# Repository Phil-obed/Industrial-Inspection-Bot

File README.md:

download TINYGPS++ library for successful compilation

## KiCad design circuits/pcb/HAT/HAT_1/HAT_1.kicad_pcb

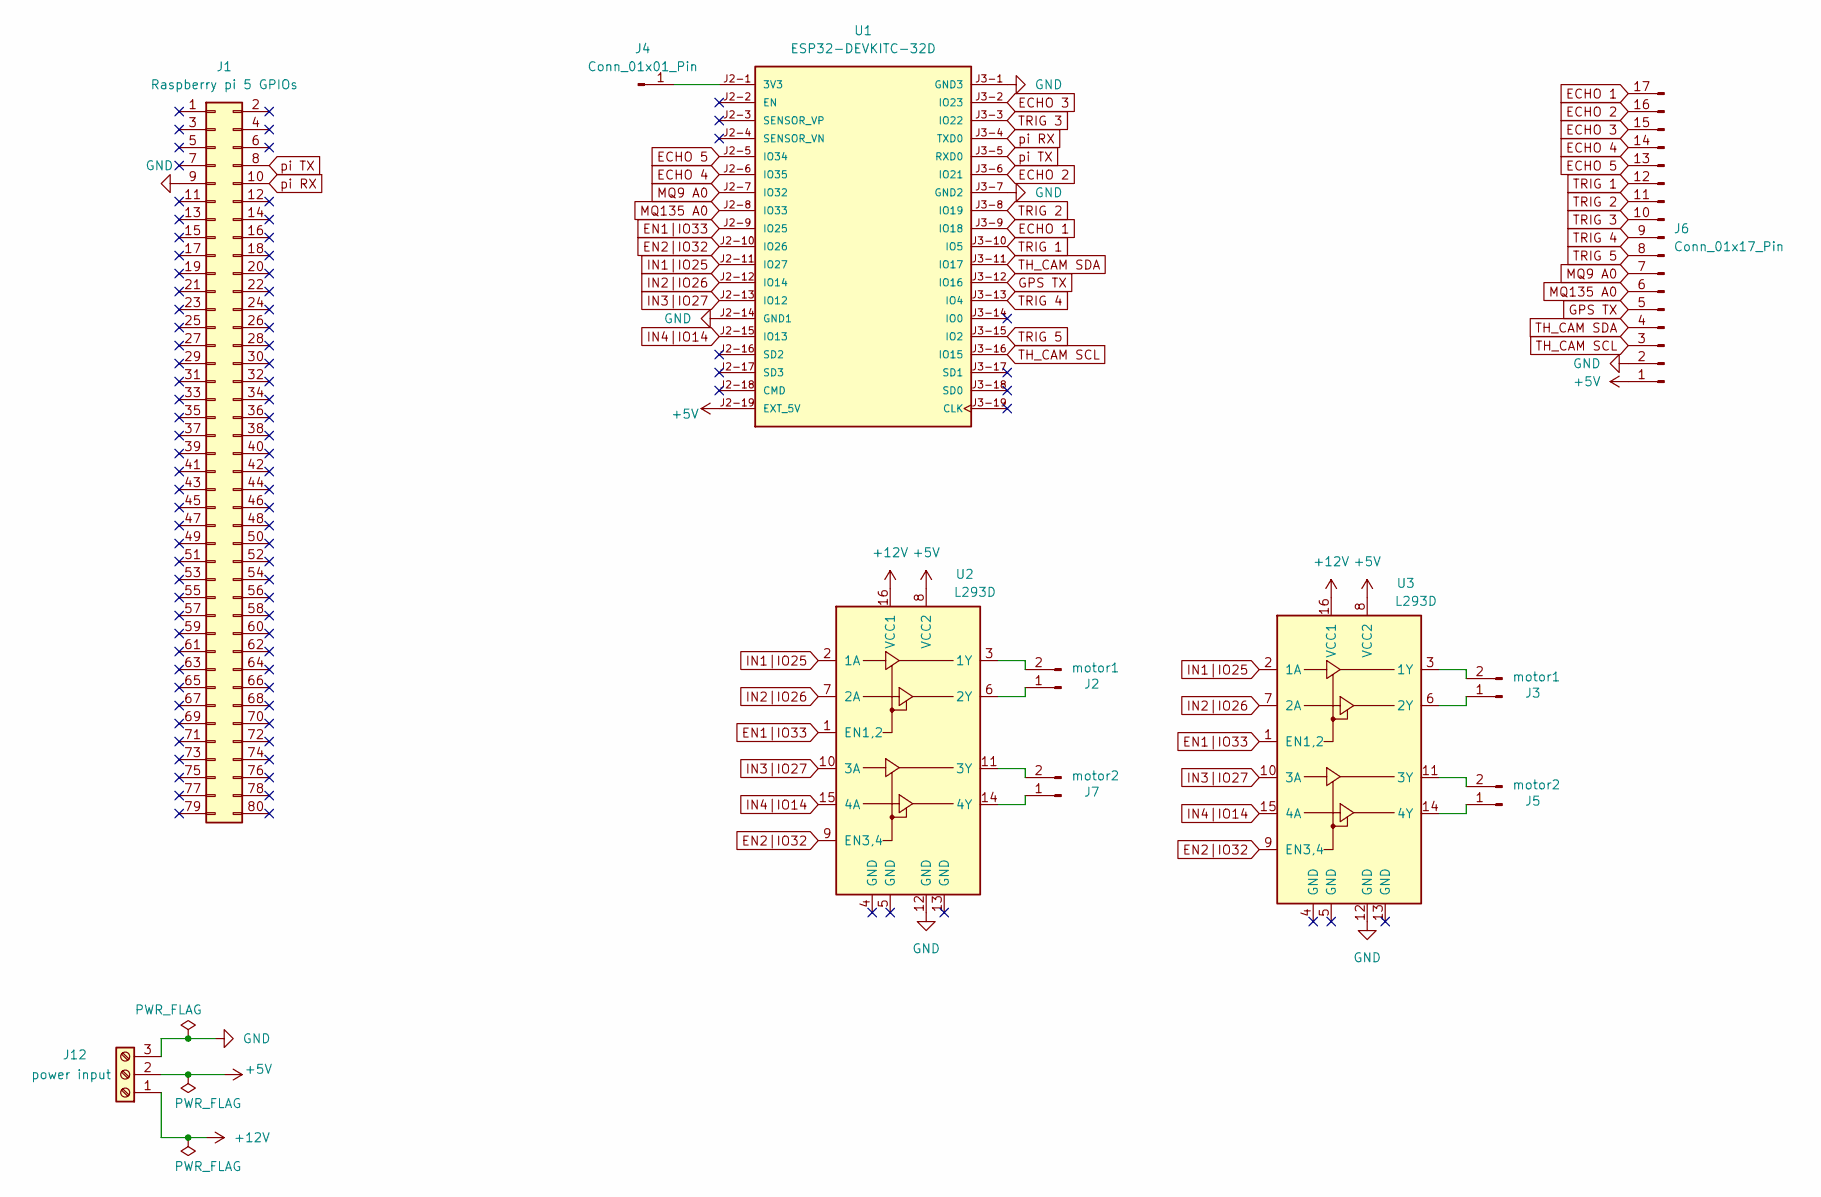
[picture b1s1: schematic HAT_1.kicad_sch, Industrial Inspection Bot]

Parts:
J1: Raspberry pi 5 GPIOs; PinHeader_2x20_P2.54mm_Vertical
J2, J3: motor1; PinHeader_1x02_P2.54mm_Vertical
J4: Conn_01x01_Pin; PinHeader_1x01_P2.54mm_Vertical
J5, J7: motor2; PinHeader_1x02_P2.54mm_Vertical
J6: Conn_01x17_Pin; PinHeader_1x17_P2.54mm_Vertical
J12: power input; TerminalBlock_CUI_TB007-508-03_1x03_P5.08mm_Horizontal
U1: ESP32-DEVKITC-32D; MODULE_ESP32-DEVKITC-32D; PARTREV V4
U2, U3: L293D; DIP-16_W7.62mm

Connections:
+5V: J6.1, J12.2, U1.J2-19 (EXT_5V), U2.8 (VCC2), U3.8 (VCC2)
+12V: J12.1, U2.16 (VCC1), U3.16 (VCC1)
ECHO 1: J6.17, U1.J3-9 (IO18)
ECHO 2: J6.16, U1.J3-6 (IO21)
ECHO 3: J6.15, U1.J3-2 (IO23)
ECHO 4: J6.14, U1.J2-6 (IO35)
ECHO 5: J6.13, U1.J2-5 (IO34)
EN1|IO33: U1.J2-9 (IO25), U2.1 (EN1,2), U3.1 (EN1,2)
EN2|IO32: U1.J2-10 (IO26), U2.9 (EN3,4), U3.9 (EN3,4)
GND: J1.9, J6.2, J12.3, U1.J2-14 (GND1), U1.J3-1 (GND3), U1.J3-7 (GND2), U2.12 (GND), U3.12 (GND)
GPS TX: J6.5, U1.J3-12 (IO16)
IN1|IO25: U1.J2-11 (IO27), U2.2 (1A), U3.2 (1A)
IN2|IO26: U1.J2-12 (IO14), U2.7 (2A), U3.7 (2A)
IN3|IO27: U1.J2-13 (IO12), U2.10 (3A), U3.10 (3A)
IN4|IO14: U1.J2-15 (IO13), U2.15 (4A), U3.15 (4A)
MQ9 A0: J6.7, U1.J2-7 (IO32)
MQ135 A0: J6.6, U1.J2-8 (IO33)
unnamed: J2.1, U2.6 (2Y)
unnamed: J2.2, U2.3 (1Y)
unnamed: J3.1, U3.6 (2Y)
unnamed: J3.2, U3.3 (1Y)
unnamed: J4.1, U1.J2-1 (3V3)
unnamed: J5.1, U3.14 (4Y)
unnamed: J5.2, U3.11 (3Y)
unnamed: J7.1, U2.14 (4Y)
unnamed: J7.2, U2.11 (3Y)
TH_CAM SCL: J6.3, U1.J3-16 (IO15)
TH_CAM SDA: J6.4, U1.J3-11 (IO17)
TRIG 1: J6.12, U1.J3-10 (IO5)
TRIG 2: J6.11, U1.J3-8 (IO19)
TRIG 3: J6.10, U1.J3-3 (IO22)
TRIG 4: J6.9, U1.J3-13 (IO4)
TRIG 5: J6.8, U1.J3-15 (IO2)
pi RX: J1.10, U1.J3-4 (TXD0)
pi TX: J1.8, U1.J3-5 (RXD0)

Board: 2 copper layers, 11 parts (1 on the bottom side), 35 nets, no tracks yet.

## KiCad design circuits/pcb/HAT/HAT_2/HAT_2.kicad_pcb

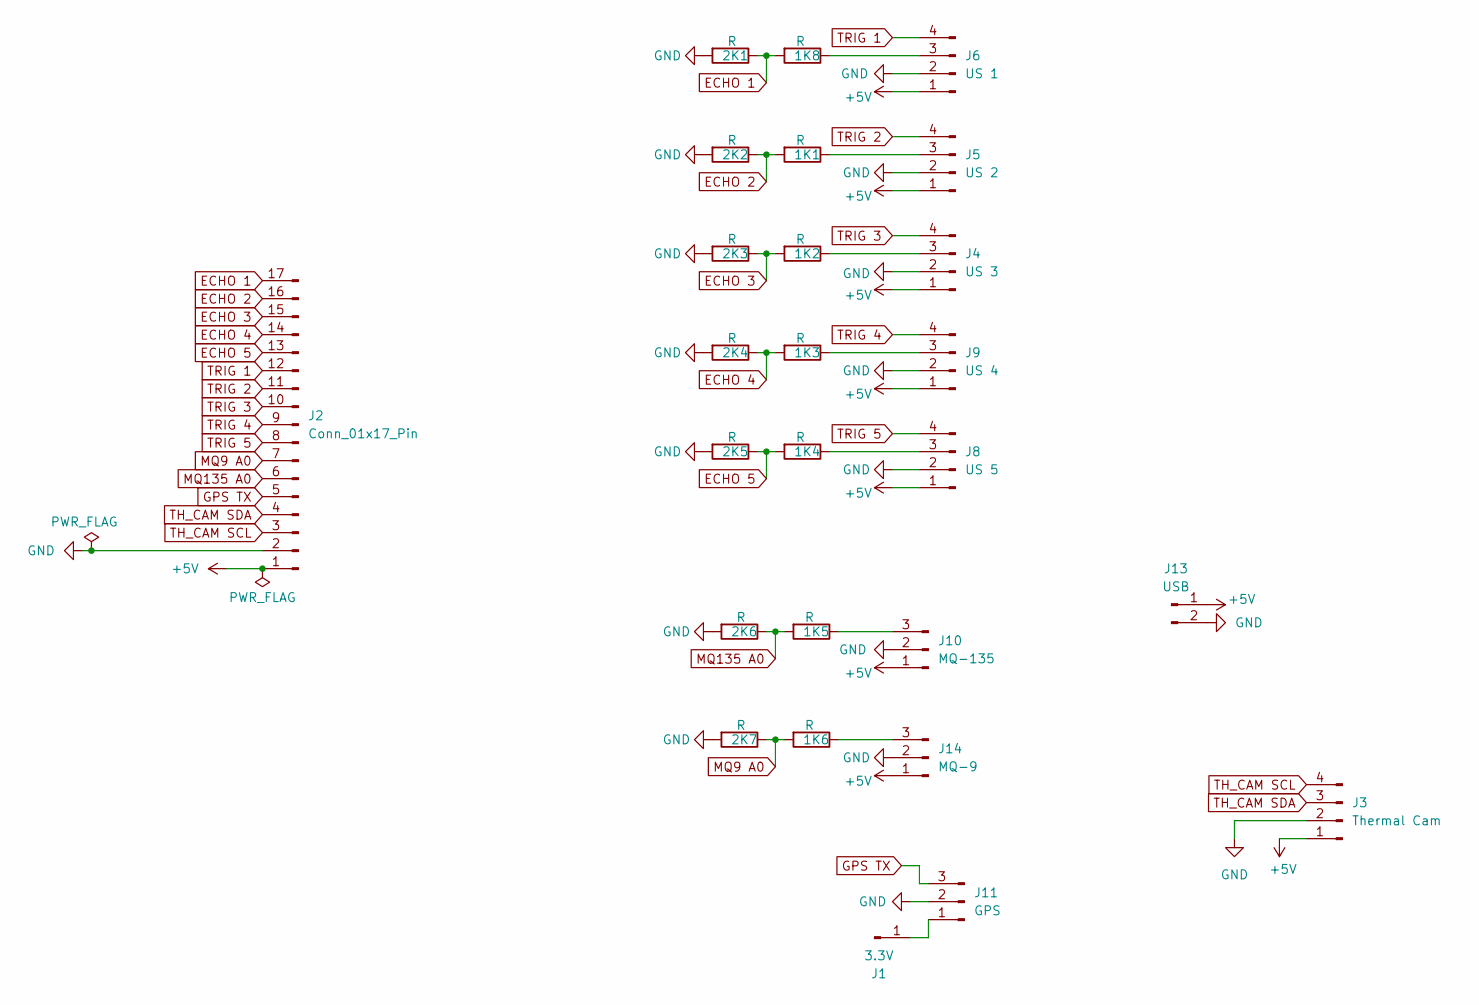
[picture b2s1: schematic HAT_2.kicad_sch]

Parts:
1K1, 1K2, 1K3, 1K4, 1K5, 1K6, 1K8, 2K1, 2K2, 2K3, 2K4, 2K5, 2K6, 2K7: R; R_Axial_DIN0207_L6.3mm_D2.5mm_P7.62mm_Horizontal
J1: 3.3V; PinHeader_1x01_P2.54mm_Vertical
J2: Conn_01x17_Pin; PinHeader_1x17_P2.54mm_Vertical
J3: Thermal Cam; PinHeader_1x04_P2.54mm_Vertical
J4: US 3; PinHeader_1x04_P2.54mm_Vertical
J5: US 2; PinHeader_1x04_P2.54mm_Vertical
J6: US 1; PinHeader_1x04_P2.54mm_Vertical
J8: US 5; PinHeader_1x04_P2.54mm_Vertical
J9: US 4; PinHeader_1x04_P2.54mm_Vertical
J10: MQ-135; PinHeader_1x03_P2.54mm_Vertical
J11: GPS; PinHeader_1x03_P2.54mm_Vertical
J13: USB; PinHeader_1x02_P2.54mm_Vertical
J14: MQ-9; PinHeader_1x03_P2.54mm_Vertical

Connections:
+5V: J2.1, J3.1, J4.1, J5.1, J6.1, J8.1, J9.1, J10.1, J13.1, J14.1
ECHO 1: 1K8.2, 2K1.1, J2.17
ECHO 2: 1K1.2, 2K2.1, J2.16
ECHO 3: 1K2.2, 2K3.1, J2.15
ECHO 4: 1K3.2, 2K4.1, J2.14
ECHO 5: 1K4.2, 2K5.1, J2.13
GND: 2K1.2, 2K2.2, 2K3.2, 2K4.2, 2K5.2, 2K6.2, 2K7.2, J2.2, J3.2, J4.2, J5.2, J6.2, J8.2, J9.2, J10.2, J11.2, J13.2, J14.2
GPS TX: J2.5, J11.3
MQ9 A0: 1K6.2, 2K7.1, J2.7
MQ135 A0: 1K5.2, 2K6.1, J2.6
unnamed: J1.1, J11.1
unnamed: 1K2.1, J4.3
unnamed: 1K1.1, J5.3
unnamed: 1K8.1, J6.3
unnamed: 1K4.1, J8.3
unnamed: 1K3.1, J9.3
unnamed: 1K5.1, J10.3
unnamed: 1K6.1, J14.3
TH_CAM SCL: J2.3, J3.4
TH_CAM SDA: J2.4, J3.3
TRIG 1: J2.12, J6.4
TRIG 2: J2.11, J5.4
TRIG 3: J2.10, J4.4
TRIG 4: J2.9, J9.4
TRIG 5: J2.8, J8.4

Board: 2 copper layers, 26 parts (0 on the bottom side), 25 nets, no tracks yet.

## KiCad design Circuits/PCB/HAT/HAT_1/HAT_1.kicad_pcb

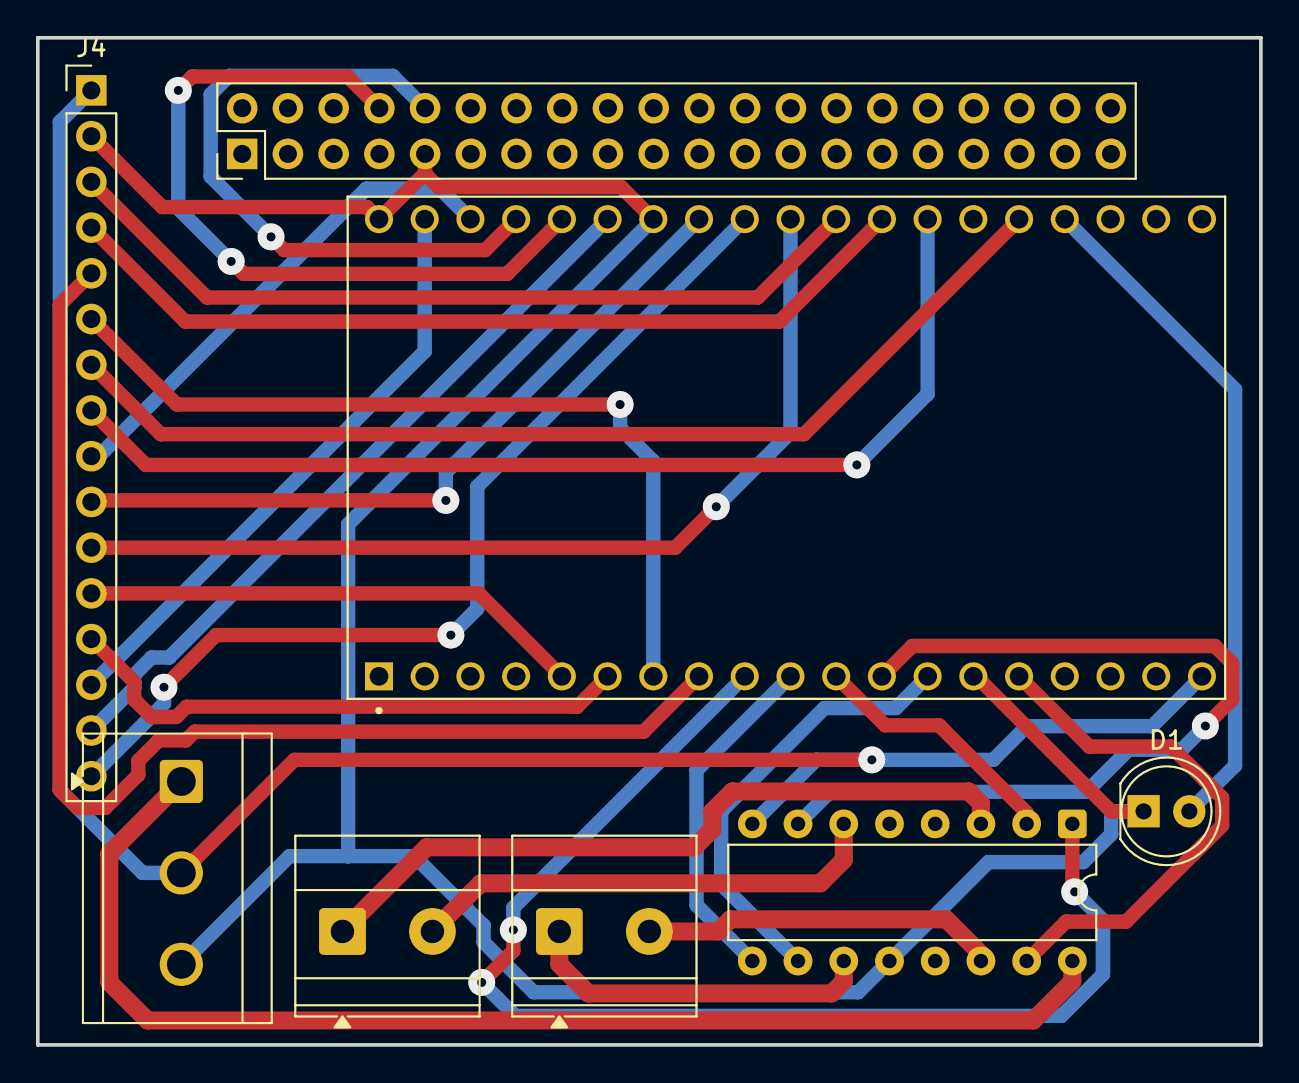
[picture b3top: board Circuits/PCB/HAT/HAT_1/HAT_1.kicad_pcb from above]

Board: 2 copper layers, 67.9 x 55.9 mm, 8 parts (0 on the bottom side), 30 nets.

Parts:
D1: LED; LED_D5.0mm
J1: Raspberry pi 5 GPIOs; PinHeader_2x20_P2.54mm_Vertical
J2: motor 1; TerminalBlock_Phoenix_MKDS-1,5-2_1x02_P5.00mm_Horizontal
J3: motor 2; TerminalBlock_Phoenix_MKDS-1,5-2_1x02_P5.00mm_Horizontal
J4: Conn_01x16_Pin; PinHeader_1x16_P2.54mm_Vertical
J12: power input; TerminalBlock_CUI_TB007-508-03_1x03_P5.08mm_Horizontal
U1: ESP32-DEVKITC-32D; MODULE_ESP32-DEVKITC-32D
U2: L293D; DIP-16_W7.62mm

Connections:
+5V: J4.1, J12.2, U1.J2-19 (EXT_5V), U2.8 (VCC2)
+12V: J12.1, U2.16 (VCC1)
ECHO 1: J4.16, U1.J3-9 (IO18)
ECHO 2: J4.15, U1.J3-6 (IO21)
ECHO 3: J4.14, U1.J3-2 (IO23)
ECHO 4: J4.13, U1.J2-6 (IO35)
ECHO 5: J4.12, U1.J2-5 (IO34)
EN1|IO33: U1.J2-9 (IO25), U2.1 (EN1,2)
EN2|IO32: U1.J2-10 (IO26), U2.9 (EN3,4)
GND: D1.1 (K), J1.9, J4.2, J12.3, U1.J2-14 (GND1), U1.J3-1 (GND3), U1.J3-7 (GND2), U2.12 (GND)
GPS RX: J4.3, U1.J3-11 (IO17)
GPS TX: J4.4, U1.J3-12 (IO16)
IN1|IO25: U1.J2-11 (IO27), U2.2 (1A)
IN2|IO26: U1.J2-12 (IO14), U2.7 (2A)
IN3|IO27: U1.J2-13 (IO12), U2.10 (3A)
IN4|IO14: U1.J2-15 (IO13), U2.15 (4A)
MQ9 A0: J4.6, U1.J2-7 (IO32)
MQ135 A0: J4.5, U1.J2-8 (IO33)
unnamed: D1.2 (A), U1.J3-16 (IO15)
unnamed: J2.1, U2.3 (1Y)
unnamed: J2.2, U2.6 (2Y)
unnamed: J3.1, U2.11 (3Y)
unnamed: J3.2, U2.14 (4Y)
TRIG 1: J4.11, U1.J3-10 (IO5)
TRIG 2: J4.10, U1.J3-8 (IO19)
TRIG 3: J4.9, U1.J3-3 (IO22)
TRIG 4: J4.8, U1.J3-13 (IO4)
TRIG 5: J4.7, U1.J3-15 (IO2)
pi RX: J1.10, U1.J3-4 (TXD0)
pi TX: J1.8, U1.J3-5 (RXD0)

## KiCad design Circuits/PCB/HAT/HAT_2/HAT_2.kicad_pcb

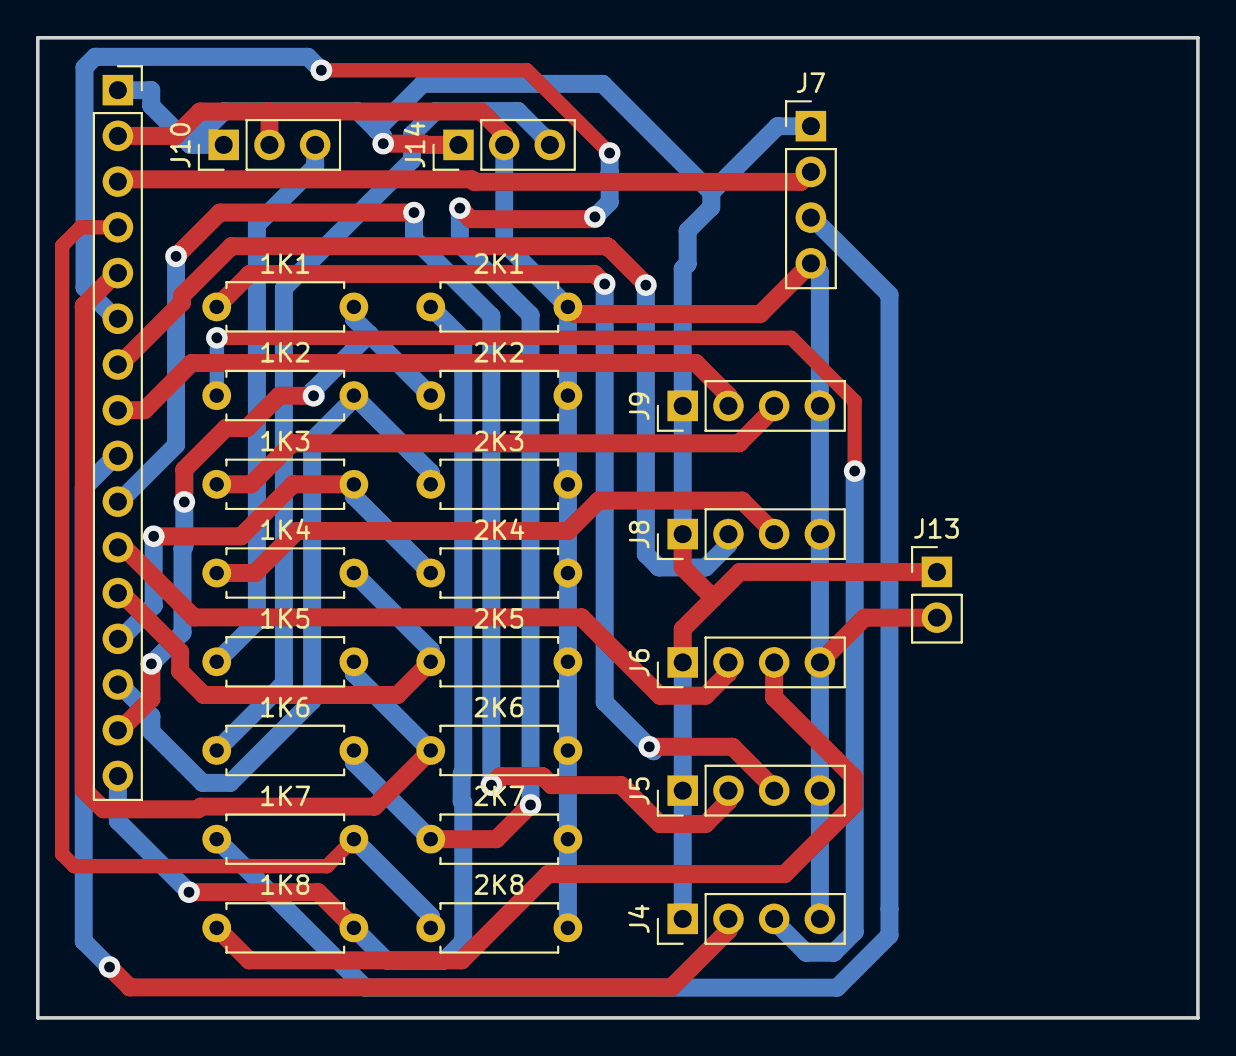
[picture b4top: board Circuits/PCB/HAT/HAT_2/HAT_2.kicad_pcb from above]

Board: 2 copper layers, 64.4 x 54.4 mm, 26 parts (0 on the bottom side), 24 nets.

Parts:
1K1, 1K2, 1K3, 1K4, 1K5, 1K6, 1K7, 1K8, 2K1, 2K2, 2K3, 2K4, 2K5, 2K6, 2K7, 2K8: R; R_Axial_DIN0207_L6.3mm_D2.5mm_P7.62mm_Horizontal
J1: Conn_01x16_Pin; PinSocket_1x16_P2.54mm_Vertical
J4: US 3; PinHeader_1x04_P2.54mm_Vertical
J5: US 2; PinHeader_1x04_P2.54mm_Vertical
J6: US 1; PinHeader_1x04_P2.54mm_Vertical
J7: GPS; PinHeader_1x04_P2.54mm_Vertical
J8: US 5; PinHeader_1x04_P2.54mm_Vertical
J9: US 4; PinHeader_1x04_P2.54mm_Vertical
J10: MQ-135; PinHeader_1x03_P2.54mm_Vertical
J13: USB; PinHeader_1x02_P2.54mm_Vertical
J14: MQ-9; PinHeader_1x03_P2.54mm_Vertical

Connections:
+5V: J1.1, J4.1, J5.1, J6.1, J7.1, J8.1, J9.1, J10.1, J13.1, J14.1
ECHO 1: 1K8.2, 2K1.1, J1.16
ECHO 2: 1K1.2, 2K2.1, J1.15
ECHO 3: 1K2.2, 2K3.1, J1.14
ECHO 4: 1K3.2, 2K4.1, J1.13
ECHO 5: 1K4.2, 2K5.1, J1.12
GND: 2K1.2, 2K2.2, 2K3.2, 2K4.2, 2K5.2, 2K6.2, 2K7.2, 2K8.2, J1.2, J4.4, J5.4, J6.4, J7.4, J8.4, J9.4, J10.2, J13.2, J14.2
GPS RX: J1.3, J7.2
GPS TX: 1K7.2, 2K8.1, J1.4
MQ9 A0: 1K6.2, 2K7.1, J1.6
MQ135 A0: 1K5.2, 2K6.1, J1.5
unnamed: 1K2.1, J4.3
unnamed: 1K1.1, J5.3
unnamed: 1K8.1, J6.3
unnamed: 1K7.1, J7.3
unnamed: 1K4.1, J8.3
unnamed: 1K3.1, J9.3
unnamed: 1K5.1, J10.3
unnamed: 1K6.1, J14.3
TRIG 1: J1.11, J6.2
TRIG 2: J1.10, J5.2
TRIG 3: J1.9, J4.2
TRIG 4: J1.8, J9.2
TRIG 5: J1.7, J8.2

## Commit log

2025-06-15 init
2025-07-24 test 1 init
2025-07-29 movement
2025-08-29 Normalize line endings
2025-08-29 Add .gitattributes and normalize line endings
2025-08-29 Add files via upload
    Thermal Camera codes
2025-08-30 Add files via upload
    Version 2
2025-09-09 obsa sim
2025-09-09 bot redesign
2025-09-10 print csv instead of serial output.
2025-09-10 output modified
2025-09-10 sim link
2025-09-10 rearange
2025-09-12 dashboard
2025-09-12 dash-console
2025-09-12 dash-Connections
2025-09-12 connections
2025-09-12 dash-map
2025-09-12 graphs
2025-09-12 bot visualisation
2025-09-12 web test complete
2025-09-12 Version 1
2025-09-13 Prev
2025-09-13 Version 1.1
2025-09-16 main
2025-09-17 main firmware RTOS
2025-09-17 main updated: Programs/main/ESP32/src/main.cpp
2025-09-17 dashboard: update console
2025-09-17 ultrasonic visualization update
2025-09-17 ultrasonic visualization ui update(ease transitions for arcs and wedges)
